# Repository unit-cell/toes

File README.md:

# toes
A device that sends USB and DIN MIDI messages using four footswitches, a sustain pedal and an expression pedal as the interface. This project is a very easy DIY build that consists of very few through-hole components, recommended for beginners!

## Software
Requirements: Bounce2 library, MIDI library (found in Arduino IDE library manager).

To set custom MIDI messages, change settings in config.h file and then compile.

## Foot switches 
They send a note on MIDI message when pressed, and a note off message when released.

## Sustain and expression pedals
The sustain pedal works the same as the foot switches. It is assumed that the sustain pedal will short the tip and sleeve of the jack while it is not pressed, and interrupt the connection when it is pressed. The code could be modified for the opposite situation.

The expression pedal sends a MIDI CC message. This design carries 5V on the tip, the wiper on the ring, and ground on the sleeve of the TRS jack.

## USB and DIN midi
The USB port on the teensy powers the unit and sends USB midi messages, and there is also a DIN MIDI out socket.

## Build guide
First solder R1, R2, the teensy pin sockets, MIDI DIN socket, and the stereo jack sockets for the pedals. All of them go on the top of the board, as shown in the picture below. **Do not solder the foot switches yet, if you are are building toes with a MIDI DIN socket**.*

Then screw the foot switches to the top panel. Solder short cables or resistor legs to the foot switch legs that will be connected to the PCB. These are the legs that *become connected when the foot switch is pressed*. Mount the PCB to the top panel with the 22 mm spacers (I used a 20 mm spacer + a nut), and solder the wire/legs to the pads highlighted by the white mark on the silkscreen.

You can trim the long legs on the bottom of the board if you are using nuts as spacers for the bottom panel. Assemble these and you are done!

Note about foot switches: it is possible to use any momentary foot switch with enough clearance to fit between the top panel and the board. Just make sure to wire it to the holes marked with a white rectangle, so that these become connected when pressing the switch.

*If you want a lower profile and don't need a MIDI DIN socket, you can get the footswitches listed in the BOM as FS5700SPMT2B2M2QE. These have solder pins instead of solder lugs and can be soldered directly on to the board.

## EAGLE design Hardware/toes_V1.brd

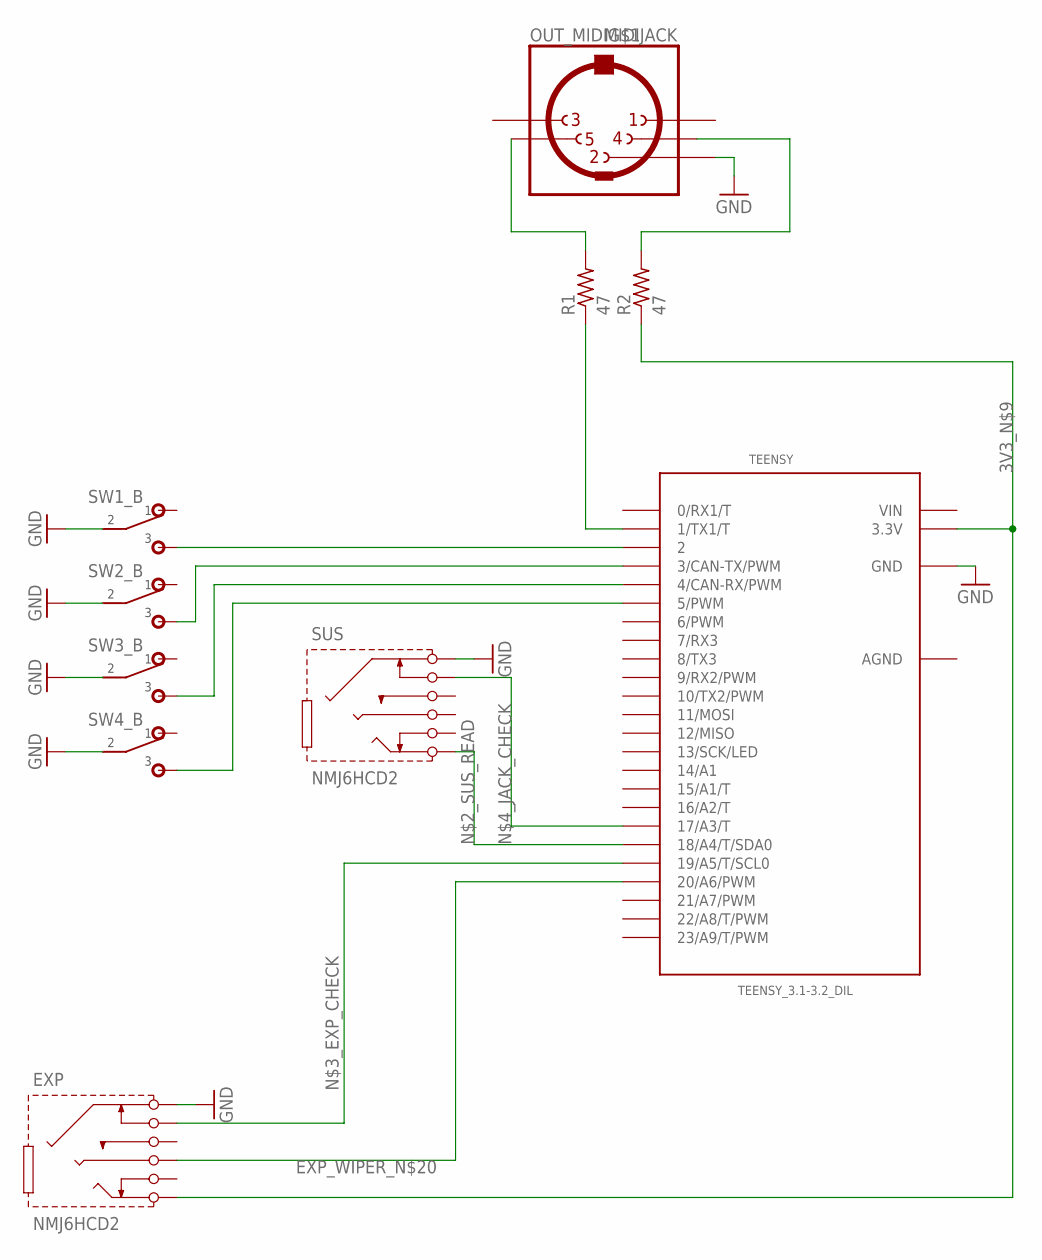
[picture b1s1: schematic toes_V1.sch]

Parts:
EXP: NMJ6HCD2
OUT_MIDI: MIDIJACK; CP-2350
R1, R2: 47; 0204/7
SUS: NMJ6HCD2
SW1, SW2, SW3, SW4: DPDTDPDT_MOM; SF12011F-0202-20R-M-011
TEENSY: TEENSY_3.1-3.2_DIL; TEENSY_3.0-3.2&LC_DIL

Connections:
3V3_N$9: EXP.T (TIP), R2.1, TEENSY.3.3V
AGND: TEENSY.AGND
EXP_WIPER_N$20: EXP.R (RING), TEENSY.20/A6 (20/A6/PWM)
GND: EXP.S (SLEEVE), OUT_MIDI.2, SUS.S (SLEEVE), SW1.P$5 (2), SW2.P$5 (2), SW3.P$5 (2), SW4.P$5 (2), TEENSY.GND
MIDI_OUT_N$8: R1.1, TEENSY.1 (1/TX1/T)
unnamed: OUT_MIDI.4, R2.2
unnamed: SUS.T (TIP), TEENSY.18/A4 (18/A4/T/SDA0)
unnamed: OUT_MIDI.5, R1.2
unnamed: EXP.SN (SLEEVE-S), TEENSY.19/A5 (19/A5/T/SCL0)
unnamed: SUS.SN (SLEEVE-S), TEENSY.17/A3 (17/A3/T)
SW1_N$14: SW1.P$6 (3), TEENSY.2
SW2_N$15: SW2.P$6 (3), TEENSY.3 (3/CAN-TX/PWM)
SW3_N$16: SW3.P$6 (3), TEENSY.4 (4/CAN-RX/PWM)
SW4_N$17: SW4.P$6 (3), TEENSY.5 (5/PWM)
VIN: TEENSY.VIN

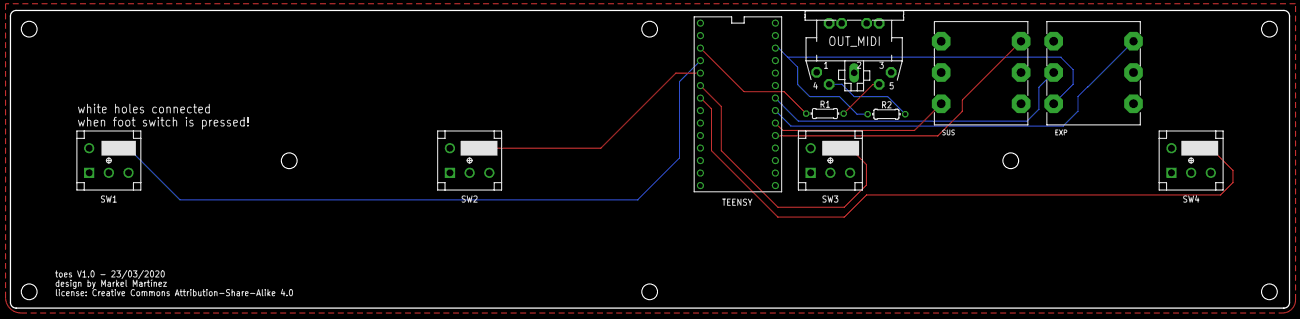
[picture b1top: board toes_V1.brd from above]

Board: 2 copper layers, 260.0 x 60.5 mm, 10 parts (0 on the bottom side), 13 nets.

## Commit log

2020-04-01 fixed MIDI DIN out
2020-04-01 added .xls BOM
2020-04-01 added BOM in csv format

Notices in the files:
Hardware/toes_V1.brd:
license: Creative Commons Attribution-Share-Alike 4.0
